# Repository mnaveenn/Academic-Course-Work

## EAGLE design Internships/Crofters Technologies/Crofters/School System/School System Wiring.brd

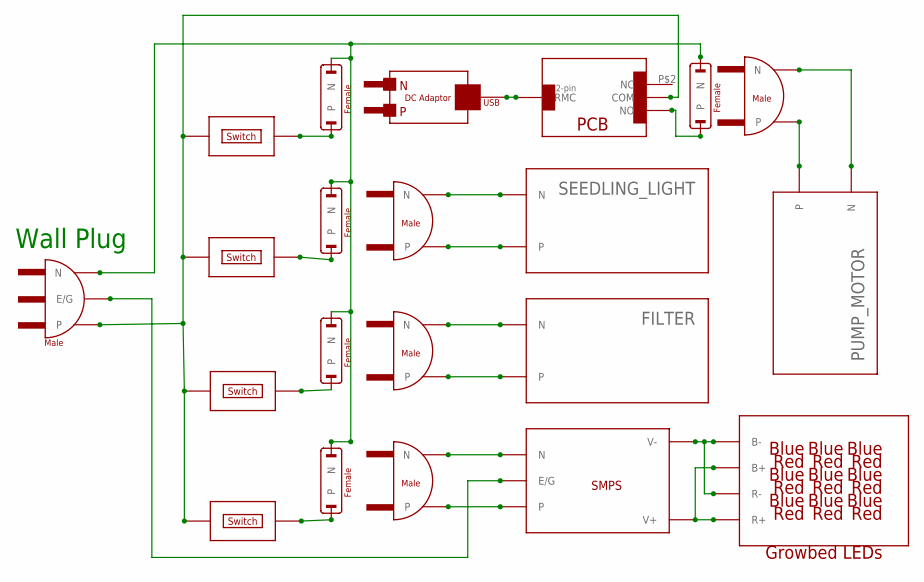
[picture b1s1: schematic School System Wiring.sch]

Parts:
FILTER: EQUIPMENT; 2PINS
PUMP_MOTOR: EQUIPMENT; 2PINS
SEEDLING_LIGHT: EQUIPMENT; 2PINS
U$1: AC-PLUG-3; 3PINS
U$2, U$3, U$4, U$5: AC-PLUG-2; 2PINS
U$6: DC_ADAPTOR; 1PIN
U$7: SCHOOL_PCB; 4PINS
U$10: GROWBED_LEDS; 4PINS
U$11, U$12, U$13, U$14: SWITCH; 2PINS
U$15: SMPS; 5PINS
X1, X2, X3, X4, X5: AC-JACK-2; 2PINS

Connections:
unnamed: U$1.2, U$11.1, U$12.1, U$13.1, U$14.1
unnamed: U$11.2, X1.1
unnamed: U$13.2, X2.1
unnamed: U$12.2, X3.1
unnamed: U$14.2, X4.1
unnamed: U$1.3 (N), X1.2 (N), X2.2 (N), X3.2 (N), X4.2 (N), X5.2 (N)
unnamed: SEEDLING_LIGHT.1, U$5.1
unnamed: SEEDLING_LIGHT.2 (N), U$5.2 (N)
unnamed: FILTER.1, U$2.1
unnamed: FILTER.2 (N), U$2.2 (N)
unnamed: U$3.1, U$15.P$3
unnamed: U$3.2 (N), U$15.P$2 (N)
unnamed: U$10.P$1 (B+), U$10.P$3 (R+), U$15.P$4 (V+)
unnamed: U$10.P$2 (B-), U$10.P$4 (R-), U$15.P$5 (V-)
unnamed: PUMP_MOTOR.1, U$4.1
unnamed: PUMP_MOTOR.2 (N), U$4.2 (N)

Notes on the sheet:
Wall Plug

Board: 2 copper layers, 21 parts (0 on the bottom side), 16 nets, no tracks yet.

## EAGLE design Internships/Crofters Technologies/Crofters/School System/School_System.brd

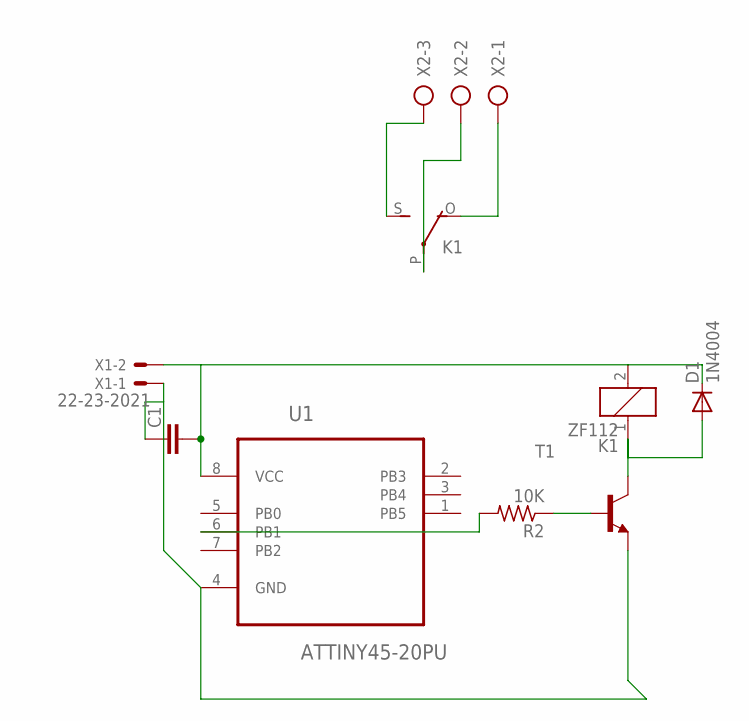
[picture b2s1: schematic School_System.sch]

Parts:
C1: C2,5-3; C2.5-3
D1: 1N4004; DO41-10
K1: ZF112
R2: 10K; 0204/7
T1: 2N2222-NPN-TO92-EBC; TO92-EBC
U1: ATTINY45-20PU; DIP254P762X533-8
X1: 22-23-2021
X2: AK300/3

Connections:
unnamed: C1.2, D1.C, K1.2, U1.8 (VCC), X1.2
unnamed: C1.1, T1.E, U1.4 (GND), X1.1
unnamed: R2.2, U1.6 (PB1)
unnamed: R2.1, T1.B
unnamed: D1.A, K1.1, T1.C
unnamed: K1.P, X2.2
unnamed: K1.S, X2.3
unnamed: K1.O, X2.1

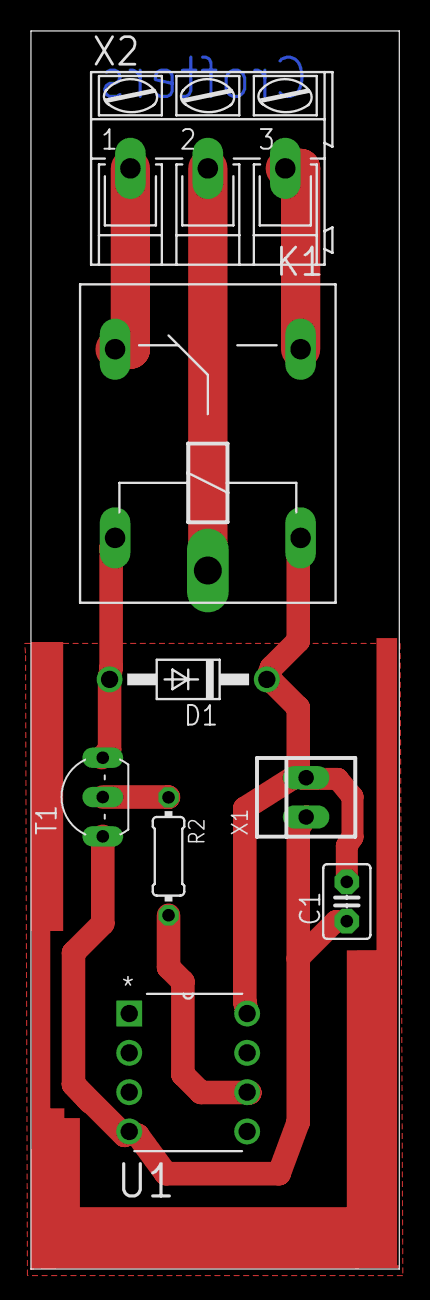
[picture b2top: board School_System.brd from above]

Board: 2 copper layers, 23.8 x 80.0 mm, 8 parts (0 on the bottom side), 8 nets.

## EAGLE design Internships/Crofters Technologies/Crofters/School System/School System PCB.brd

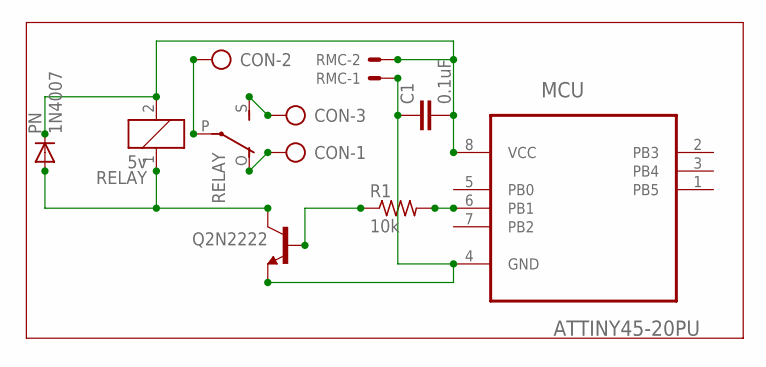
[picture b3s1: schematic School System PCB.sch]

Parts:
C1: 0.1uF; C2.5-3
CON: AK300/3
MCU: ATTINY45-20PU; DIP254P762X533-8
PN: 1N4007; DO41-10
Q2N2222: 2N2222-NPN-TO92-EBC; TO92-EBC
R1: 10k; 0204/7
RELAY: 5v; ZF112
RMC: 22-23-2021

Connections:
unnamed: C1.2, MCU.8 (VCC), PN.C, RELAY.2, RMC.2
unnamed: C1.1, MCU.4 (GND), Q2N2222.E, RMC.1
unnamed: MCU.6 (PB1), R1.2
unnamed: Q2N2222.B, R1.1
unnamed: PN.A, Q2N2222.C, RELAY.1
unnamed: CON.2, RELAY.P
unnamed: CON.3, RELAY.S
unnamed: CON.1, RELAY.O

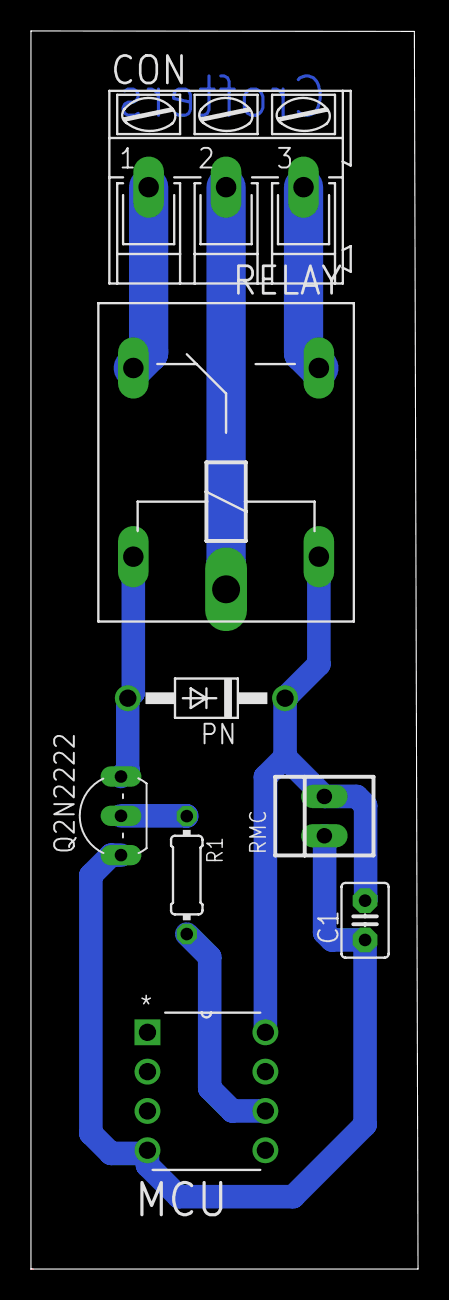
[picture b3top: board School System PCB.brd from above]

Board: 2 copper layers, 25.0 x 80.0 mm, 8 parts (0 on the bottom side), 8 nets.

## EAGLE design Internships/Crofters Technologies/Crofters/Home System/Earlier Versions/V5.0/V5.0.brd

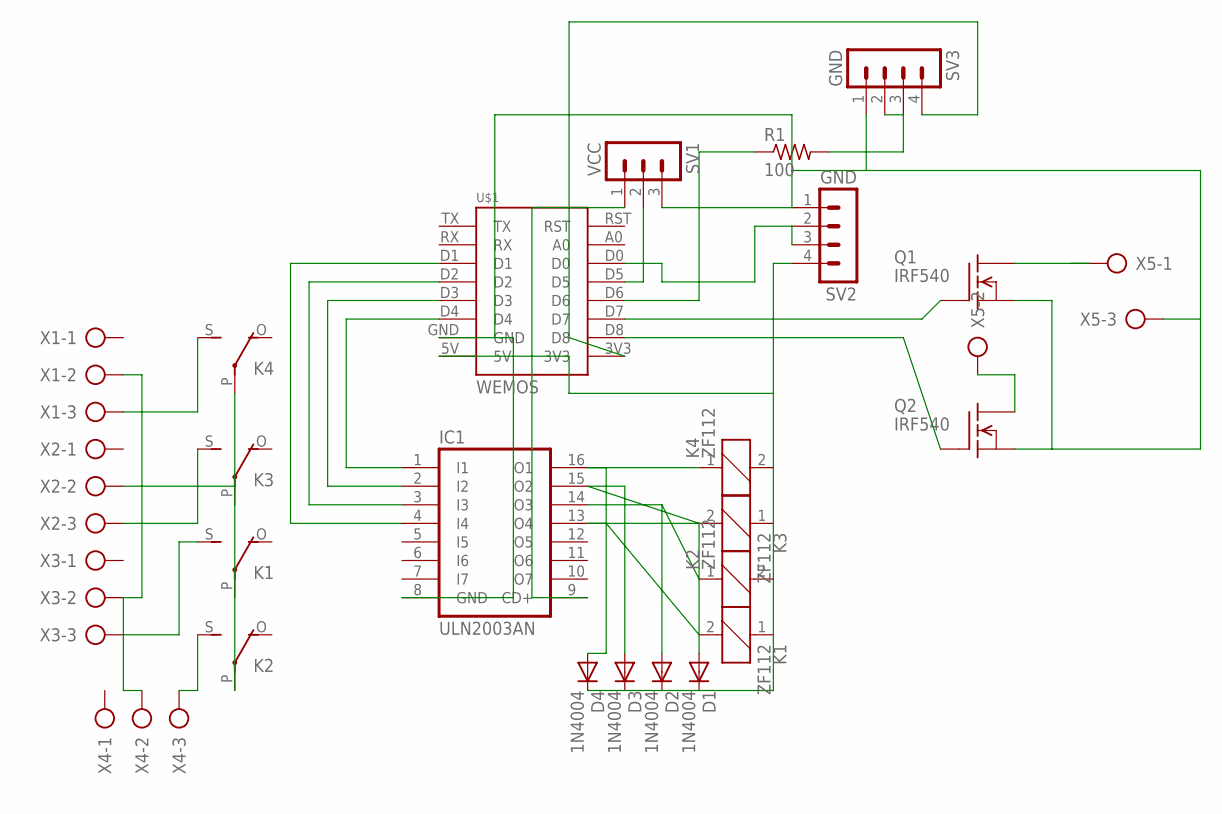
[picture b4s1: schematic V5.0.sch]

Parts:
D1, D2, D3, D4: 1N4004; DO41-10
IC1: ULN2003AN; DIL16
K1, K2, K3, K4: ZF112
Q1, Q2: IRF540; TO220
R1: 100; 0207/7
SV1: VCC; MA03-1
SV2, SV3: GND; MA04-1
U$1: WEMOS
X1, X2, X3, X4, X5: AK300/3

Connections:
unnamed: IC1.4 (I4), U$1.D1
unnamed: IC1.3 (I3), U$1.D2
unnamed: IC1.2 (I2), U$1.D3
unnamed: IC1.1 (I1), U$1.D4
unnamed: IC1.8 (GND), Q1.3 (S), Q2.3 (S), SV1.3, SV2.1, SV3.1, U$1.GND, X5.3
unnamed: D1.C, D2.C, D3.C, D4.C, IC1.9 (CD+), K1.1, K2.2, K3.1, K4.2, SV1.1, SV2.4, U$1.5V
unnamed: D3.A, IC1.15 (O2), K3.2
unnamed: D1.A, IC1.13 (O4), K1.2
unnamed: D2.A, IC1.14 (O3), K2.1
unnamed: D4.A, IC1.16 (O1), K4.1
unnamed: K4.S, X1.3
unnamed: K3.S, X2.3
unnamed: K1.S, X3.3
unnamed: K2.S, X4.3
unnamed: K1.P, K2.P, K3.P, K4.P, X1.2, X2.2, X3.2, X4.2
unnamed: SV1.2, U$1.D5
unnamed: SV2.2, SV2.3, U$1.D0
unnamed: SV3.4, U$1.3V3
unnamed: Q1.1 (G), U$1.D7
unnamed: Q2.1 (G), U$1.D8
unnamed: Q1.2 (D), X5.1
unnamed: Q2.2 (D), X5.2
unnamed: R1.2, SV3.2, SV3.3
unnamed: R1.1, U$1.D6

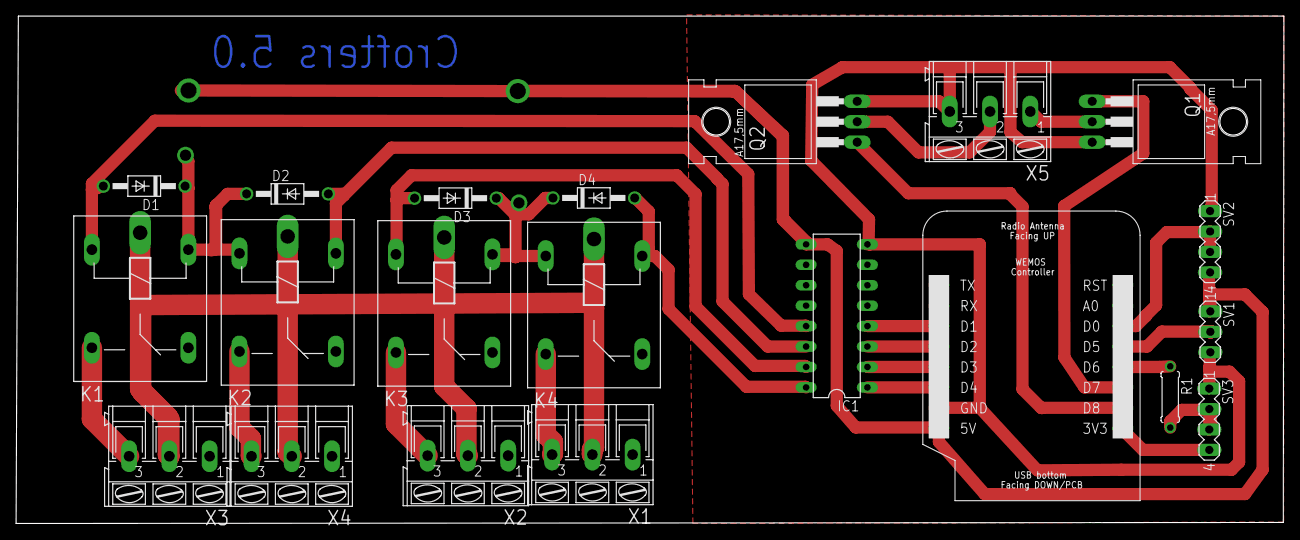
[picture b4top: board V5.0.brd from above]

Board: 2 copper layers, 157.6 x 63.1 mm, 21 parts (0 on the bottom side), 24 nets.

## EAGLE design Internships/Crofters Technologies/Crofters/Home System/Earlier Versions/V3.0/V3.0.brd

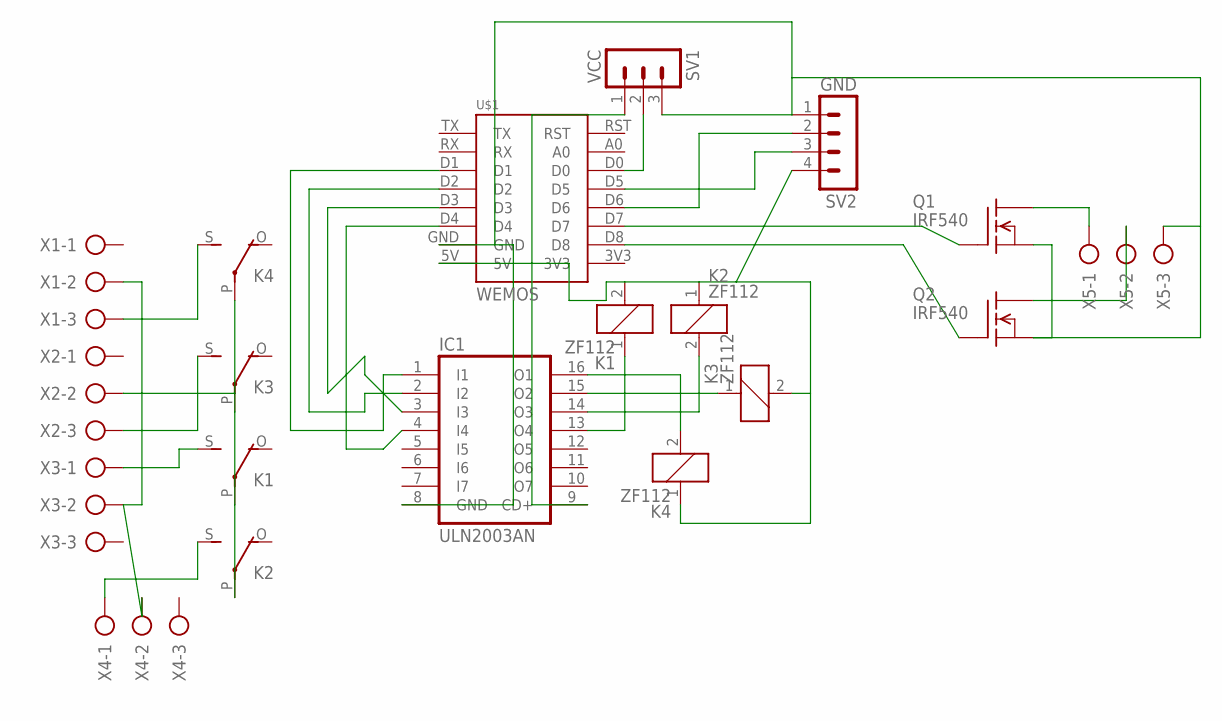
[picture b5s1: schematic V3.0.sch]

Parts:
IC1: ULN2003AN; DIL16
K1, K2, K3, K4: ZF112
Q1, Q2: IRF540; TO220
SV1: VCC; MA03-1
SV2: GND; MA04-1
U$1: WEMOS
X1, X2, X3, X4, X5: AK300/3

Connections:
unnamed: IC1.1 (I1), U$1.D1
unnamed: IC1.2 (I2), U$1.D2
unnamed: IC1.3 (I3), U$1.D3
unnamed: IC1.4 (I4), U$1.D4
unnamed: IC1.8 (GND), Q1.3 (S), Q2.3 (S), SV1.3, SV2.1, U$1.GND, X5.3
unnamed: IC1.9 (CD+), K1.2, K2.1, K3.2, K4.1, SV1.1, SV2.4, U$1.5V
unnamed: IC1.15 (O2), K3.1
unnamed: IC1.13 (O4), K1.1
unnamed: IC1.14 (O3), K2.2
unnamed: IC1.16 (O1), K4.2
unnamed: K4.S, X1.3
unnamed: K3.S, X2.3
unnamed: K1.S, X3.1
unnamed: K2.S, X4.1
unnamed: K1.P, K2.P, K3.P, K4.P, X1.2, X2.2, X3.2, X4.2
unnamed: SV1.2, U$1.D0
unnamed: SV2.3, U$1.D5
unnamed: SV2.2, U$1.D6
unnamed: Q1.1 (G), U$1.D7
unnamed: Q2.1 (G), U$1.D8
unnamed: Q1.2 (D), X5.1
unnamed: Q2.2 (D), X5.2

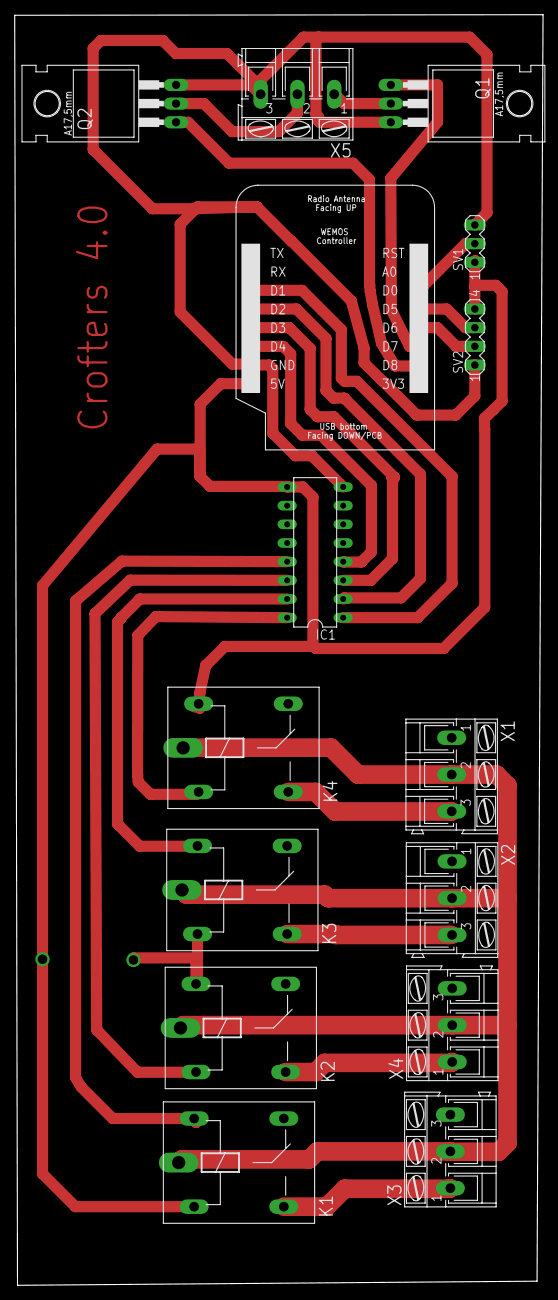
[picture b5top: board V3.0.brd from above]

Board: 2 copper layers, 71.9 x 172.8 mm, 15 parts (0 on the bottom side), 22 nets.

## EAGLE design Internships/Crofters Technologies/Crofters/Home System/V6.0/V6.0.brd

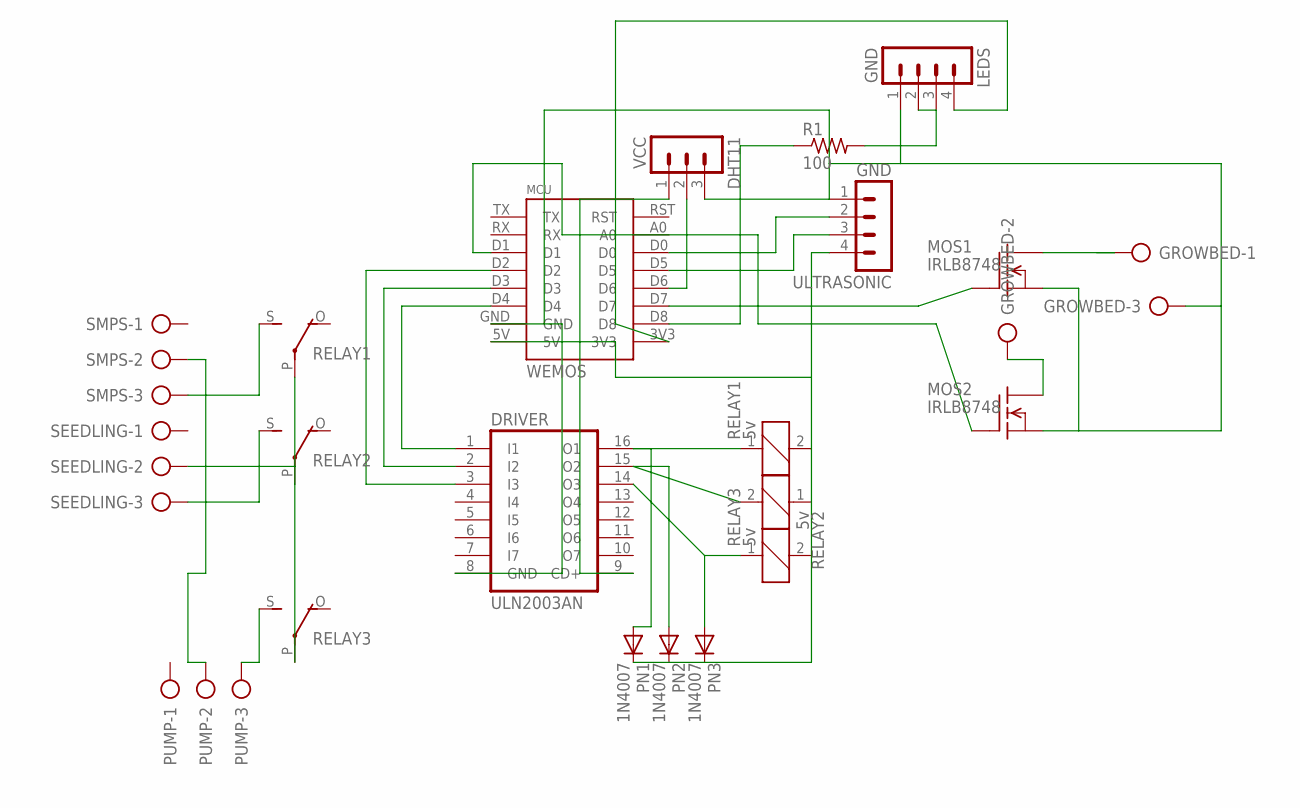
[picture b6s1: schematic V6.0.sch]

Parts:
DHT11: VCC; MA03-1
DRIVER: ULN2003AN; DIL16
GROWBED: AK300/3
LEDS: GND; MA04-1
MCU: WEMOS
MOS1, MOS2: IRLB8748; TO220
PN1, PN2, PN3: 1N4007; DO41-10
PUMP: AK300/3
R1: 100; 0207/7
RELAY1, RELAY2, RELAY3: 5v; ZF112
SEEDLING: AK300/3
SMPS: AK300/3
ULTRASONIC: GND; MA04-1

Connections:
unnamed: MCU.D5, ULTRASONIC.3
unnamed: DRIVER.3 (I3), MCU.D2
unnamed: DRIVER.2 (I2), MCU.D3
unnamed: DRIVER.1 (I1), MCU.D4
unnamed: DHT11.3, DRIVER.8 (GND), GROWBED.3, LEDS.1, MCU.GND, MOS1.3 (S), MOS2.3 (S), ULTRASONIC.1
unnamed: DHT11.1, DRIVER.9 (CD+), MCU.5V, PN1.C, PN2.C, PN3.C, RELAY1.2, RELAY2.1, RELAY3.2, ULTRASONIC.4
unnamed: DRIVER.15 (O2), PN2.A, RELAY2.2
unnamed: DHT11.2, MCU.D6
unnamed: DRIVER.14 (O3), PN3.A, RELAY3.1
unnamed: DRIVER.16 (O1), PN1.A, RELAY1.1
unnamed: RELAY1.S, SMPS.3
unnamed: RELAY2.S, SEEDLING.3
unnamed: PUMP.3, RELAY3.S
unnamed: PUMP.2, RELAY1.P, RELAY2.P, RELAY3.P, SEEDLING.2, SMPS.2
unnamed: MCU.D0, ULTRASONIC.2
unnamed: LEDS.4, MCU.3V3
unnamed: MCU.D7, MOS1.1 (G)
unnamed: MCU.D1, MOS2.1 (G)
unnamed: GROWBED.1, MOS1.2 (D)
unnamed: GROWBED.2, MOS2.2 (D)
unnamed: LEDS.2, LEDS.3, R1.2
unnamed: MCU.D8, R1.1

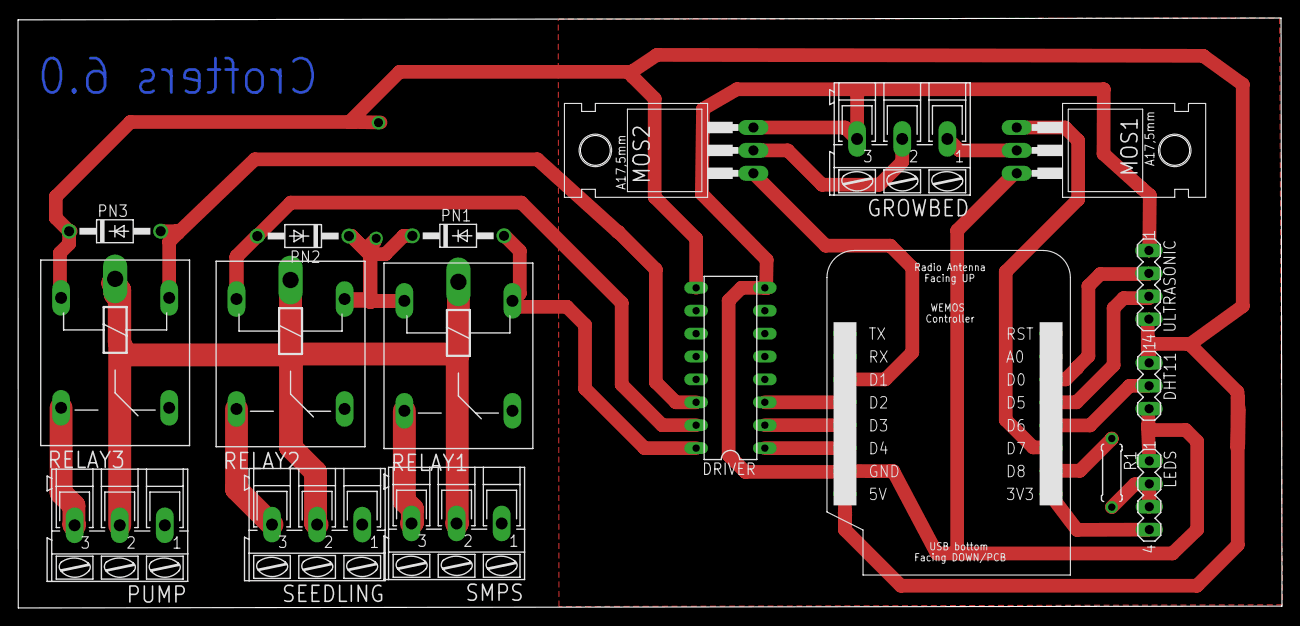
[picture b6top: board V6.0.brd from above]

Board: 2 copper layers, 140.2 x 65.4 mm, 18 parts (0 on the bottom side), 22 nets.

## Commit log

2020-01-29 Efficient Monaural Speech Separation System using Ideal Binary Mask (IBM)
    Final Year Project at SSNCE under Dr. R. Rajavel
    Efficient Monaural Speech Separation System using Ideal Binary Mask (IBM)
2020-01-29 Time, Compute and Space Efficient Mass File Data Transfer to Cloud
    Project in Data Structures and Algorithms
    Project Memebers: Naveen Narayanan and Praneeth Chandra Thota
    Time, Compute and Space Efficient Mass File Data Transfer to Cloud
2020-01-29 Algorithmic Cryptocurrency Trading System
    Rutgers University
    Algorithmic Cryptocurrency Trading System
    Project Members: Yash Nisar and Naveen Narayanan Meyyappan
    Subject: Massive Data Storage and Retrieval
2020-01-29 Uniq Technologies Embedded Systems
    Uniq Technologies - Embedded Systems
2020-01-29 Crofters Technologies
    Crofters Technologies
2020-01-29 Workshops
    Workshops
2020-01-29 Voice Based Indoor Navigation system for Visually Impaired
    Voice Based Indoor Navigation system for Visually Impaired
    Project Members: Vimalraj, Sivasankar, Prakash, Ravishankar, Somasundar, Naveen
    Project Guide: Dr. R. Rajavel, Dr. Joseph Gladwin
2020-01-29 Certificates
    Certificates
2020-01-29 Probability and Statistics
    Probability and Statistics
2020-02-11 Added the HTML 5 course certificate
    Added HTML 5 course
2020-02-11 Removing Project Instructions
    Removing Project Instructions
2020-02-11 Added HTML course work
    coursework added
